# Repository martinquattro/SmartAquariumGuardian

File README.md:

# Smart Aquarium Guardian

Smart Aquarium Guardian is an ESP32-based IoT aquarium monitoring and automation system for hobbyists and small-scale aquariums. It combines real-time sensing, automated feeding, remote telemetry, and a local touchscreen interface to help maintain a healthy aquarium with minimal manual effort.

## Overview

This project monitors key aquarium conditions such as water temperature and TDS, supports scheduled feeding, and publishes telemetry to an MQTT broker such as ThingsBoard. It also provides a local user interface built with LVGL so the device can be controlled directly on the hardware.

The system is designed for users who want to:
- monitor aquarium conditions in real time
- receive alerts when values move outside safe thresholds
- automate feeding routines
- configure and control the device remotely

## Key Features

- Real-time monitoring
  - DS18B20 temperature sensing
  - TDS water quality measurement
  - configurable thresholds and alerts

- Automated feeding
  - servo-based food dispenser
  - up to 10 daily feeding schedules
  - manual feeding support

- Connectivity and telemetry
  - Wi-Fi connectivity with automatic reconnection
  - MQTT-based telemetry and remote control
  - access point mode for initial device configuration

- User interface
  - LVGL-based touchscreen UI
  - live sensor values and status indicators
  - feeding and system controls

- System management
  - RTC-based time synchronization
  - timezone-aware scheduling
  - EEPROM-backed configuration storage
  - battery-aware power handling

## System Architecture

The overall system consists of sensors, a control unit, a local display, and cloud connectivity.

### Main building blocks
- Sensors: temperature, TDS, and power monitoring
- Embedded controller: ESP32 firmware and local logic
- Actuators: servo feeder and display backlight/control
- Connectivity: Wi-Fi, MQTT, and remote configuration
- Cloud backend: optional ThingsBoard telemetry and command handling

## Firmware Architecture

The firmware is organized into logical layers for clarity and maintainability.

### Layered structure
- Core: shared abstractions, lifecycle patterns, and platform interfaces
- Managers: orchestration of system behavior
- Services: domain-specific logic such as storage and power management
- Drivers: hardware abstraction for sensors and actuators
- Connectivity: Wi-Fi, MQTT, and access-point configuration

For more details, see [src/core/README.md](src/core/README.md).

## Hardware Requirements

The current implementation targets an ESP32-based hardware platform and uses the following components:

- ESP32 development board
- DS18B20 temperature sensor
- TDS sensor with analog input
- servo motor for feeding mechanism
- ILI9341 SPI display with touch support
- optional RTC and EEPROM modules
- USB power with battery backup support

## Software Stack

- PlatformIO
- ESP-IDF
- C++17
- LVGL 9.1.0
- MQTT
- nlohmann-json
- Doxygen for API documentation

## Getting Started

### Prerequisites

- PlatformIO
- ESP-IDF 5.1 or newer
- Python 3.8+
- Doxygen

### Clone the Repository

```bash
git clone https://github.com/your-username/SmartAquariumGuardian.git
cd SmartAquariumGuardian
```

### Build the Project

```bash
pio run -e prod
```

### Flash the Firmware

```bash
pio run -e prod -t upload
```

### Monitor Serial Output

```bash
pio device monitor
```

## Configuration

Main configuration values are defined in [include/config.h](include/config.h) and [platformio.ini](platformio.ini).

Common settings you may want to customize:
- GPIO pin assignments
- MQTT broker address and credentials
- telemetry update interval
- sensor thresholds
- feeding schedules

> Security note: avoid committing sensitive credentials to version control. Prefer local configuration files or environment-based secrets for deployment.

## Usage

After flashing the device:

1. power on the ESP32
2. connect to the device configuration access point if prompted
3. configure Wi-Fi credentials
4. connect to the MQTT broker or cloud backend
5. use the local touchscreen UI or remote commands to interact with the system

The device will begin monitoring sensors, publishing telemetry, and executing scheduled feeds automatically.

## Project Structure

- [src](src): application source code
- [include](include): project-wide configuration headers
- [framework](framework): shared hardware and utility abstractions
- [components](components): third-party and project-local components
- [docs](docs): documentation and supporting assets
- [scripts](scripts): helper scripts such as documentation generation

## Documentation

API documentation is generated with Doxygen.

```bash
doxygen Doxyfile
```

The generated documentation is placed under [docs](docs).

## License

This project is licensed under the MIT License. See [LICENSE](LICENSE) for details.

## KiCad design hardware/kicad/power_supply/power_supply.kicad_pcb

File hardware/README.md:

# Hardware Design - Smart Aquarium Guardian

This directory serves as the central repository for all electronic design files (EDA) related to the **Smart Aquarium Guardian** project. The hardware architecture is modular, consisting of the Main Controller Board and the Power Supply Board.

## 📂 Modules

### 1. Main Controller Board (Current Active Project)
This is the core of the system, responsible for:
* **Processing:** ESP32 Microcontroller logic.
* **Sensing:** Interfaces for TDS (Total Dissolved Solids) and Temperature sensors.
* **Actuation:** Control signals for external peripherals.

### 2. Power Supply Board
Provides mains-independent operation with USB charging and battery backup. Key features:
* **USB Type-C Input:** Power-only 6P receptacle for 5V charging.
* **Li-ion/LiPo Charging:** TP4056 1A linear charger for single-cell batteries (4.2V).
* **Battery Backup:** Automatic switch to battery when USB power is lost (power path switching via P-Channel MOSFET).
* **Boost Output:** MT3608 step-up DC-DC converter to supply stable 5V from battery to the main controller.
* **Status Indicators:** Red (charging) and green (charged) LEDs.
* **Output:** Connector for main board power supply.

## 🛠️ Directory Structure & Portability

The project is designed using **KiCad EDA**. It is structured to be **fully self-contained**, meaning no external global libraries are required to view or edit the files.

```text
/kicad
├── .gitignore                   # gitignore file for this folder
├── smart_aquarium_guardian/     # Main Controller Board
│   ├── lib/                     # Project-specific Local Libraries
│   │   ├── *.kicad_sym          # Custom Schematic Symbols
│   │   └── Guardian.pretty/     # Custom PCB Footprints
│   ├── datasheets/              # Technical documentation for critical components
│   ├── fp-lib-table             # Footprint Library Table (Maps local footprints)
│   ├── sym-lib-table            # Symbol Library Table (Maps local symbols)
│   ├── smart_aquarium_guardian.kicad_pro
│   ├── smart_aquarium_guardian.kicad_sch
│   └── smart_aquarium_guardian.kicad_pcb
│
└── power_supply/                # Power Supply Board
    ├── lib/                     # Power Supply Local Libraries
    │   ├── Power_Supply.kicad_sym
    │   └── PowerSupply.pretty/
    ├── production/              # Manufacturing outputs (Gerbers, BOM, drill files)
    ├── fp-lib-table
    ├── sym-lib-table
    ├── power_supply.kicad_pro
    ├── power_supply.kicad_sch
    └── power_supply.kicad_pcb
```

## 🚀 Usage & Workflow

To ensure the integrity of the design and library links, please follow these steps:

### Prerequisites
* **Software:** KiCad EDA
* **Version:** **9.0** or later.
  * *Note: Files saved in KiCad 9.0 are not backward compatible with older versions (6.0/7.0/8.0).*

### How to Open
1. **Clone the Repository:**
   Ensure you have the full directory structure, as the project relies on relative paths.
2. **Launch KiCad:**
   Open the desired project file (`.kicad_pro`):
   * Main Controller: `kicad/smart_aquarium_guardian/smart_aquarium_guardian.kicad_pro`
   * Power Supply: `kicad/power_supply/power_supply.kicad_pro`
3. **Access Design Files:**
   * **Schematic:** Open the Schematic Editor (`.kicad_sch`) to view the logical connections.
   * **PCB Layout:** Open the PCB Editor (`.kicad_pcb`) to view the physical routing and placement.

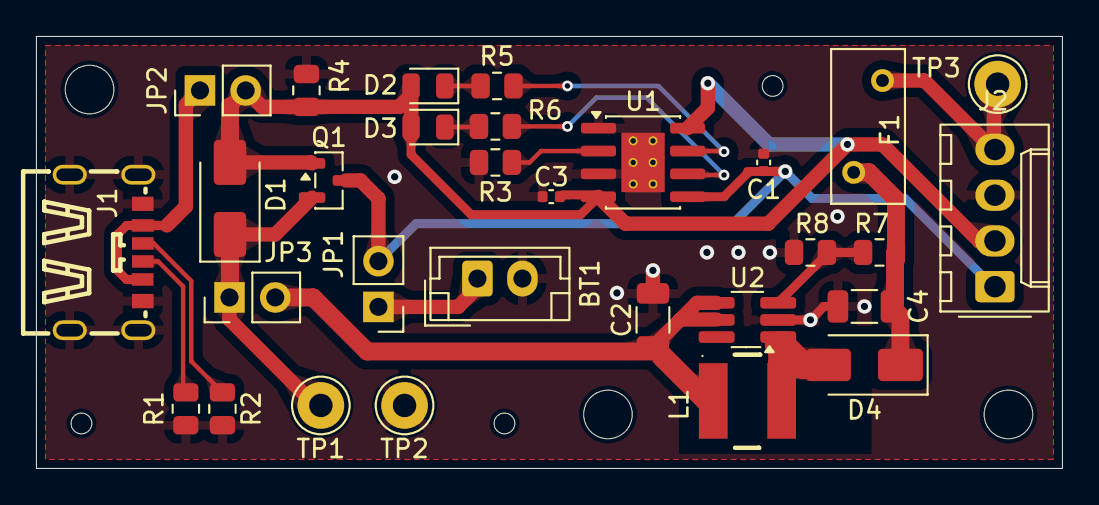
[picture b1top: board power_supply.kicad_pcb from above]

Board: 2 copper layers, 57.0 x 24.0 mm, 36 parts (0 on the bottom side), 18 nets.

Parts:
BT1: Battery_Cell; JST_EH_B2B-EH-A_1x02_P2.50mm_Vertical
C1, C3: 10uF; C_0402_1005Metric
C2, C4: 22uF; C_1206_3216Metric
D1, D4: SS34; D_SMA
D2: RED; LED_0805_2012Metric
D3: GREEN; LED_0805_2012Metric
F1: Fuse; Fuse_BelFuse_0ZRE0005FF_L8.3mm_W3.8mm
J1: USB_C_Receptacle_PowerOnly_6P; TYPE-C-SMD_TYPE-C-6P
J2: PINHD_1x4_Female; Molex_KK-254_AE-6410-04A_1x04_P2.54mm_Vertical
JP1: Bat; PinHeader_1x02_P2.54mm_Vertical
JP2: usb; PinHeader_1x02_P2.54mm_Vertical
JP3: power; PinHeader_1x02_P2.54mm_Vertical
L1: 10uH; IND-SMD_2P-L5.0-W5.0
M1, M2, M6: MountingHole_2.7mm
M3, M4, M5: MountingHole_2.2mm_M2
Q1: AO3401A; SOT-23
R1, R2: 5.1k; R_0805_2012Metric
R3: 2.4k; R_0805_2012Metric
R4: 100k; R_0805_2012Metric
R5, R6: 1k; R_0805_2012Metric
R7: 110k; R_0805_2012Metric
R8: 15k; R_0805_2012Metric
TP1: TestPoint; Pin_D1.3mm_L11.0mm
TP2: gnd; Pin_D1.3mm_L11.0mm
TP3: out; Pin_D1.3mm_L11.0mm
U1: TP4056-42-ESOP8; SOIC-8-1EP_3.9x4.9mm_P1.27mm_EP2.41x3.3mm_ThermalVias
U2: MT3608; TSOT-23-6_HandSoldering

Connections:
/Boost_{OUT}: C4.1, D4.1 (K), F1.1, R7.1
GND: BT1.2 (-), C1.2, C2.2, C3.2, C4.2, J1.7 (SHIELD), J1.A12 (GND), J1.B12 (GND), J2.3 (GND), R1.2, R2.2, R3.2, R4.2, R8.2, TP2.1, U1.1 (TEMP), U1.3 (GND), U1.9 (EPAD), U2.2 (GND)
unnamed: BT1.1 (+), JP1.1 (A)
unnamed: D1.1 (K), JP3.1 (A), Q1.2 (S), TP1.1
unnamed: D2.1 (K), R5.1
unnamed: D3.1 (K), R6.1
unnamed: D4.2 (A), L1.2, U2.1 (SW)
unnamed: J1.A5 (CC1), R2.1
unnamed: J1.B5 (CC2), R1.1
unnamed: F1.2, J2.4 (Vout), TP3.1
unnamed: J1.A9 (VBUS), J1.B9 (VBUS), JP2.1 (A)
unnamed: C2.1, JP3.2 (B), L1.1, U2.4 (EN), U2.5 (IN)
unnamed: R3.1, U1.2 (PROG)
unnamed: R5.2, U1.7 (~CHRG)
unnamed: R6.2, U1.6 (~STDBY)
unnamed: R7.2, R8.1, U2.3 (FB)
V_{bat}: C1.1, J2.1 (VBat), JP1.2 (B), Q1.3 (D), U1.5 (BAT)
V_{in}: C3.1, D1.2 (A), D2.2 (A), D3.2 (A), J2.2 (Vusb), JP2.2 (B), Q1.1 (G), R4.1, U1.4 (V_{CC}), U1.8 (CE)

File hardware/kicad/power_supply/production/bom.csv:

Designator,Footprint,Quantity,Value,LCSC Part #
"C1, C3",0402,2,10uF,C15525
"C2, C4",1206,2,22uF,C12891
"D1, D4",D_SMA,2,SS34,C8678
D2,0805,1,RED,C84256
D3,0805,1,GREEN,C2297
J1,TYPE-C-SMD_TYPE-C-6P,1,USB_C_Receptacle_PowerOnly_6P,C456012
L1,IND-SMD_2P-L5.0-W5.0,1,10uH,C9389
Q1,SOT-23,1,AO3401A,C15127
"R1, R2",0805,2,5.1k,C27834
R3,0805,1,2.4k,C17526
R4,0805,1,100k,C149504
"R5, R6",0805,2,1k,C17513
R7,0805,1,110k,C17422
R8,0805,1,15k,C17475
U1,SOIC-8-1EP_3.9x4.9mm_P1.27mm_EP2.41x3.3mm_ThermalVias,1,TP4056-42-ESOP8,C16581
U2,TSOT-23-6_HandSoldering,1,MT3608,C84817

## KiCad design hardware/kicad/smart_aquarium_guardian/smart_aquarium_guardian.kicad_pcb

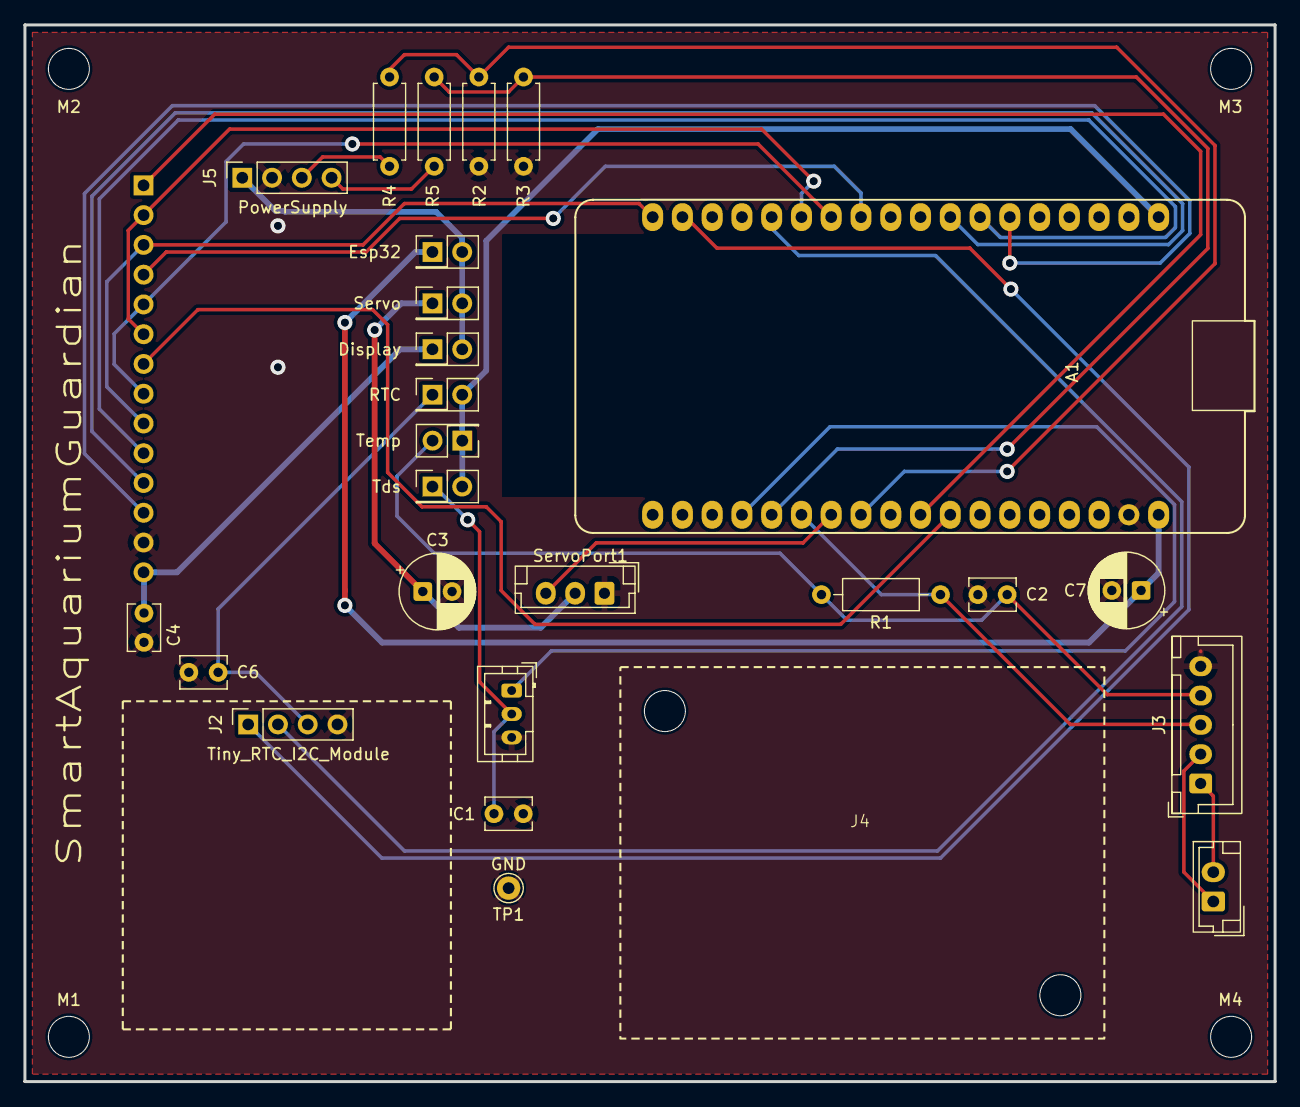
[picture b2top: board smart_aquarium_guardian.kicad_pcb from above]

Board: 2 copper layers, 106.7 x 90.2 mm, 29 parts (1 on the bottom side), 29 nets.

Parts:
A1: ESP32_DevKit1.1; DOIT_ESP32_DEVKIT_36Pins
C1, C2, C4, C6: 100n; C_Disc_D3.8mm_W2.6mm_P2.50mm
C3: 470u; CP_Radial_D6.3mm_P2.50mm
C7: 1000u; CP_Radial_D6.3mm_P2.50mm
J1: Display_2.8_TFT_240xRGBx320; PinSocket_1x14_P2.54mm_Vertical
J2: Tiny_RTC_I2C_Module; PinSocket_1x04_P2.54mm_Vertical
J3: SensorsInput; JST_XH_B5B-XH-A_1x05_P2.50mm_Vertical
J4: TdsMeter; tds_meter_module
J5: PowerSupply; PinSocket_1x04_P2.54mm_Vertical
JP1: Display; PinHeader_2x01_P2.54mm_Vertical
JP2: RTC; PinHeader_2x01_P2.54mm_Vertical
JP3: Servo; PinHeader_2x01_P2.54mm_Vertical
JP4: Temp; PinHeader_2x01_P2.54mm_Vertical
JP5: Esp32; PinHeader_2x01_P2.54mm_Vertical
JP6: Tds; PinHeader_2x01_P2.54mm_Vertical
M1, M2, M3, M4: MountingHole_3.5mm
R1: 4K7; R_Axial_DIN0207_L6.3mm_D2.5mm_P10.16mm_Horizontal
R2: 22K; R_Axial_DIN0207_L6.3mm_D2.5mm_P7.62mm_Horizontal
R3, R5: 100K; R_Axial_DIN0207_L6.3mm_D2.5mm_P7.62mm_Horizontal
R4: 10K; R_Axial_DIN0207_L6.3mm_D2.5mm_P7.62mm_Horizontal
ServoPort1: MG90s_Micro_servo; JST_EH_B3B-EH-A_1x03_P2.50mm_Vertical
TP1: GND; Pin_D1.0mm_L10.0mm

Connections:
3V3: A1.1 (3.3V), JP2.2 (B), JP4.1 (A), JP6.2 (B)
5V: J5.1 (VCC), JP1.2 (B), JP3.2 (B), JP5.2 (B)
/LED_BKL: A1.29 (ADC2_CH6/D14), J1.7 (LED)
/LED_CS: A1.6 (D15), J1.12 (CS)
/LED_CS_{touch}: A1.11 (D5), J1.4 (T_CS)
/LED_DO: A1.7 (D2), J1.10 (DO)
/LED_IRQ_{touch}: A1.28 (ADC2_CH7/D27), J1.1 (T_IRQ)
/LED_RST: A1.8 (D4), J1.11 (RESET)
/LED_SCK: A1.12 (D18), J1.5 (T_CLK), J1.8 (SCK)
/LED_SDI: A1.18 (D23), J1.3 (T_DIN), J1.9 (SDI)
/LED_SDO: A1.13 (D19), J1.2 (T_DO), J1.6 (SDO)
/RTC_SCL: A1.17 (D22/SCL), J2.1 (SCL)
/RTC_SDA: A1.14 (D21/SDA), J2.2 (SDA)
/SERVO_PWM: A1.25 (ADC1_CH5/D33), ServoPort1.1 (IN1)
/TDS_DATA: A1.22 (ADC1_CH6/D34), J4.1
/TEMP_DATA: A1.24 (ADC1_CH4/D32), J3.3, R1.1
/V_BAT*: A1.23 (ADC1_CH7/D35), R3.2, R5.1
/V_USB*: A1.26 (DAC1/ADC2_CH8/D25), R2.2, R4.1
GND: A1.35 (GND), C1.2, C2.2, C3.2, C4.2, C6.2, C7.2, J1.13 (GND), J2.4 (GND), J3.5, J4.3, J5.2 (GND), R2.1, R3.1, ServoPort1.3, TP1.1
unnamed: A1.36 (VIN), C7.1, JP5.1 (A)
unnamed: C4.1, J1.14 (VCC), JP1.1 (A)
unnamed: C6.1, J2.3 (VCC), JP2.1 (A)
unnamed: J3.1, J4.5
unnamed: J3.2, J4.4 (Pin_5)
unnamed: C1.1, J4.2, JP6.1 (A)
unnamed: J5.4 (VBAT), R5.2
unnamed: J5.3 (VUSB), R4.2
unnamed: C3.1, JP3.1 (A), ServoPort1.2
unnamed: C2.1, J3.4, JP4.2 (B), R1.2

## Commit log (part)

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2025-08-07 Modify .gitignore
2025-08-07 Update .gitignore to include additional build artifacts
2025-08-07 Clear ignore files
2025-08-07 Remove ignore files
2025-08-07 Implement SmartAquariumGuardian class
2025-08-13 Add core framework and driver implementations for Smart Aquarium Guardian
2025-08-14 Add CMake and PlatformIO config
2025-08-14 Refactor DigitalOut to DigitalInOut for GPIO control
    Replaces DigitalOut with a new DigitalInOut class supporting input, output, and input/output modes. Updates relevant includes and implementation files, and adds a BUILTIN_LED pin definition in config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
2025-08-15 Add Delay utility and integrate in SmartAquariumGuardian
    Introduced a Delay class for periodic timing in ESP32 projects. Integrated Delay into SmartAquariumGuardian to control update intervals, improving timing and reducing flickering with a debounce delay.
2025-08-16 Refactor AnalogIn for calibrated voltage reading
    Reworked AnalogIn to use ESP-IDF ADC calibration for accurate voltage readings. Deprecated raw and normalized read methods, added ReadCalibrated for millivolt output, and updated pin-to-channel conve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
2025-08-16 Add WaterMonitor subsystem and refactor TdsSensor
    Introduces the WaterMonitor subsystem for managing water quality monitoring, including TDS readings. Refactors TdsSensor to encapsulate analog reading storage and averaging logic, and updates SmartAq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
2025-08-16 Refactor TdsSensor analog reading and calculation
    Renamed internal variables for clarity, implemented TDS calculation using temperature compensation, and updated logging. Improved averaging logic and replaced legacy code with a more accurate ppm con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
2025-08-18 Init Temperature Sensor class and One Wire Driver
2025-08-18 Refactor config.h
2025-08-19 Initialize FoodFeeder class
2025-08-26 Misc changes
2025-08-26 Add LcdDisplay and UserInterface classes
    Working with some text samples in the Update
2025-09-06 Servo class adjustments
2025-09-07 I2C driver init
2025-09-07 EepromMemory class initialization
2025-09-08 Addition of RealTimeClock class
2025-09-17 Rename System folder to Components
2025-09-25 Add WiFiCom class for non-blocking WiFi connectivity management
2025-09-26 Refactor project structure and add IoT manager
2025-10-25 Add MQTT client integration and update WiFiCom API
    Introduced a new MQTT client wrapper (esp-mqtt) with publish/subscribe API in src/connectivity/mqtt_client.{h,cpp}. Updated CMake and PlatformIO configuration to include MQTT and custom partition tab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
2025-10-25 Mock sensor readings with random values
2025-10-25 Init periodic telemetry sending via MQTT
2025-10-26 Enhance water monitor and UI with live sensor data
    Added methods to WaterMonitor for retrieving live temperature and TDS readings, and exposed WiFi/MQTT connection status in NetworkController. Updated UserInterface to display real-time sensor values 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
2025-10-26 Refactor network and connectivity state machines
    Introduces IDLE state and Start() methods for both WiFiCom and MqttClient, improving state transitions and initialization. Refactors NetworkController to use explicit state transitions for WiFi, time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
2025-10-26 Correct typo
2025-11-02 Add RPC command handling to NetworkController
    Introduces a new network_commands.h header defining RPC command and parameter names. Refactors NetworkController to register and handle RPC commands using a callback mechanism, with initial support f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
2025-11-18 network config update
2025-11-22 Add RPC handler framework and temperature limits support
    Introduces a generic RPC handler interface and a specific handler for setting temperature limits. Refactors NetworkController to dispatch MQTT messages and handle RPC requests using the new handler s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
2025-11-22 Add feeding schedule RPC handlers
    Introduced AddFeedingScheduleHandler, DeleteFeedingScheduleHandler, and FeedNowHandler classes to handle new RPC commands for feeding schedules. Registered these handlers in NetworkController and upd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
2025-11-22 Refactor time sync and telemetry, move comms utilities
    Refactored time synchronization logic into RealTimeClock service and updated GuardianProxy and interfaces accordingly. Introduced a TelemetryData class for telemetry JSON serialization. Moved and upd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
2025-11-24 Add timezone support to time synchronization
    Introduces the ability to specify a timezone when initializing time synchronization. Adds a new RPC handler for setting the timezone, updates interfaces and implementations to accept a timezone param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
2025-12-03 Refactor time sync to accept timezone and return Result
    Updated the time synchronization initialization to accept an optional timezone parameter and return a Result object for better error handling. The interface and implementations were updated according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
2025-12-03 Add enabled flags for temperature limits in RPC handler
    Introduces TEMP_LIMIT_MIN_ENABLED and TEMP_LIMIT_MAX_ENABLED attributes to network_config.h and updates SetTempLimitsHandler to validate and handle these flags. The handler now checks if limit values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
2025-12-05 Refactor config storage and add temp limit support
    Replaces IDataStore with IStorageService and updates GuardianProxy and related interfaces to support saving and retrieving temperature limits with enable flags. Refactors configuration storage to use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
2025-12-06 Add async food feeding with dose control
    Introduces AsyncWorker for running background tasks and integrates it into FoodFeeder to allow asynchronous feeding of a specified dose. Updates IFoodFeeder and GuardianProxy interfaces to support do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
2025-12-06 Add feeding status LED indicator support
    Introduced a simple LED driver and integrated a feeding status indicator LED into the user interface. Updated the food feeder logic to toggle the indicator during feeding sequences. Added relevant in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
2025-12-06 Add feeding schedule management functionality
    Introduces feeding schedule entry management, including new interfaces and implementations for adding or modifying feeding schedule entries. Updates the storage service and memory config data to supp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
2025-12-07 Implement scheduled feeding and add minute-based time utility
    Added a method to retrieve the feeding schedule from storage and integrated scheduled feeding logic into FoodFeeder::Update, triggering feedings at scheduled times. Introduced DateTime::ToMinutesOfDa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
2025-12-08 Refactor OneWire pin control and timing
    Calls Release() in the constructor for initial pin state. Adjusts timing in Reset() for presence detection. Simplifies DriveLow() and Release() methods to set pin level instead of changing direction 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
2025-12-08 Add localization framework and integrate i18n support
    Introduces a localization service with language files and auto-generated string IDs for internationalization. Updates water monitor logic to use localized messages, adds i18n automation script, and c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
2025-12-11 Missing files from previous commit
2025-12-11 Migrate from LCD to graphic display with LVGL
    Replaces the old 20x4 LCD display driver with a new ILI9341 graphic display driver using LVGL and XPT2046 touch support. Updates pin assignments and configuration for the new display, removes LCD-spe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
2025-12-12 Add UIElement abstraction for LVGL text elements
    Introduced the UIElement class in GraphicDisplay to encapsulate LVGL label creation, text, and status color management. Added font size and status enums, and a CreateTextElement method for flexible U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
2026-01-05 Integrate new UI system and refactor display logic
    Replaces custom UI element creation and management in GraphicDisplay and UserInterface with a new UI system generated by SquareLine Studio. Adds the src/ui directory with generated C files, images, a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
2026-01-05 Add temperature out-of-limits alert to UI
    Introduces IsTemperatureOutOfLimits() in WaterMonitor and GuardianProxy to check if the temperature is outside configured limits. Updates UserInterface to visually indicate an alert state on the temp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
2026-01-05 Add double click touch callback to GraphicDisplay
    Introduces a callback mechanism for double click touch events in GraphicDisplay, allowing external handlers to be registered. Updates touch detection to use the top layer, and sets up a double click 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
2026-01-11 Add display brightness control and update sensor logic
    Introduced backlight brightness control to GraphicDisplay using PWM, including new SetBrightness method and constructor parameter. Fixed temperature and TDS sensor averaging logic to use correct thre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
2026-01-11 Improve OneWire concurrency and add CRC to temperature sensor
    Added critical section protection to OneWire operations for thread safety. Implemented CRC8 validation for DS18B20 temperature sensor readings and improved error handling for invalid readings. Disabl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
2026-01-13 Improve analog input voltage reading accuracy
    AnalogIn now averages multiple ADC samples for more accurate voltage readings and uses a default reference voltage of 1.1V. The TdsSensor uses 64 samples for its readings, and the temperature sensor 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
2026-01-28 Add PowerController service and integrate power status
    Introduce a new PowerController service to monitor battery voltage and USB power. Adds src/services/power_controller.h/.cpp implementing a singleton with Init(), GetCurrentMode(), and GetBatteryLevel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
2026-02-07 Add KiCad hardware project for aquarium guardian
    Add a self-contained KiCad hardware project for the Smart Aquarium Guardian. Changes include: updated root .gitignore (add *.ini and docs/), new hardware/.gitignore and hardware/README.md with KiCad 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
2026-02-07 Add Doxygen config and auto-gen script
    Add Doxygen configuration and integrate automatic documentation generation into the PlatformIO build.
2026-02-08 Create esp-bsp
2026-02-08 Create esp_lcd_touch_xpt2046 componente
2026-02-14 Add core base module classes and README
    Introduce the foundational Core module for the project: adds a README and base abstractions (Module, Singleton, Manager, Driver, Service).
2026-02-14 Hook up new class bases for all Drivers, Managers and Services
2026-02-14 Add AP portal and integrate WiFi config flow
    Introduce an Access Point configuration portal and wire it into the network state machine.
2026-02-15 Add long-press and safe AP/WiFi takeover
    Introduce long-press support in GraphicDisplay (new SetOnLongPressAction, callback storage, LVGL long-press time, and event handling) and simplify double-click handling.
2026-02-15 Incorporate AP Portal icon into Display
2026-02-15 Incorporate battery icons in Display LCD based on power mode
2026-02-15 Add battery mode handling and related updates
    Introduce battery-mode detection into the Module base.
2026-02-22 Add KiCad power_supply project and libs
    Add a complete KiCad power_supply project under hardware/kicad/power_supply. Includes project files (.kicad_pro, .kicad_sch, .kicad_pcb), library tables (fp-lib-table, sym-lib-table), footprints and 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
2026-02-28 First draft completed for the power supply kicad project
2026-03-03 Update datasheets
2026-03-03 Remove unnecesary footprint and symbol libraries
2026-03-08 Add sync device functionality on boot up and rpc handler
2026-03-08 Add WiFi ssid and intensity into client attributes being sent
2026-03-08 Hook up TDS rpcs, handlers, display logic
2026-03-14 Refactor MQTT configuration: remove MQTT handling from APPortal, add MQTT client configuration constants, and update HTML content for WiFi setup.
2026-03-15 Enhance SmartAquariumGuardian initialization and update methods to accept delay parameters, improving power management during startup and updates. Adjust UserInterface brightness handling for better 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
2026-03-15 Update SmartAquariumGuardian and UserInterface initialization to include delay parameters, enhance UI screen loading with splash screen.
2026-03-15 Add initializing animation into screen
2026-05-22 Visual changes on KiCAD projects
